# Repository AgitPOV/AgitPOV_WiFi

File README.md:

#  AgitPOV Wifi: 24-RGB LED dual sided POV with Wifi (ESP8266)

 (c) 2011-2017
 Contributors over the years for this version

* Thomas Ouellet Fredericks - Debuging, Accelerometer and LED engine and animation code
* Alexandre Castonguay
* Andre Girard andre@andre-girard.com
* Alan Kwok
* Sofian Audry
* Mariangela Aponte Nuñez
* Jean-Pascal Bellemare
* Daniel Felipe Valencia dfvalen0223@gmail.com
* Alex Keeling

[FR] Cette version utilise une puce ESP8266 qui permet de programmer un mot à partir de n'importe quelle connexion WiFi.
Les DELs RVB seront pré-assemblées pour que les ateliers se concentrent sur la sélection des mots que nous aimerions voir
dans nos roues de vélo, et de passer plus de temps à parcourir la ville. Les batteries sont rechargeables donc les POVs 
seront utiles plus longtemps et finalement, nous travaillons avec un designer industriel qui va développer un boitier résistant, 
imperméable et facile à placer et retirer des rayons. Tous les fichiers sont ici et nous produisons les plaquettes et les 
boitiers sous peu!

[ES] Este versión usa a un ESP8266 que permite de programar una palabra desde un dispositivo WiFi. Usamos DELs 
premontados porque los talleres se vuelven en intercambios sobre las palabras que quérémos ver en nuestra ruedas 
de bicicletas y también de pasar más tiempo juntas en una rodada. Baterías están rescargable y trabajamos con un 
diseñador sobre cajas, durables, resistente al agua y fácil de poner y quitar de los rayos de nuestras bicis. Los 
archivos están aquí y vamos a producir los plaquetas y cajas de pronto!

[EN] This version uses an ESP8266 board that let's you program your word from a WiFi device. Surface mount RGB LEDs 
(APA102C) are already soldered so we spend more time discussing what words to put on our bikes and get more time out 
in the city together. The batteries are rechargeable so people can keep using their POVs longer. Finally, we are working 
with an industrial designer so we can get sturdy, water resistant cases that are easy to put in and out of your spokes. 
All the basic files are here and we'll let you know when the boards and cases are ready!

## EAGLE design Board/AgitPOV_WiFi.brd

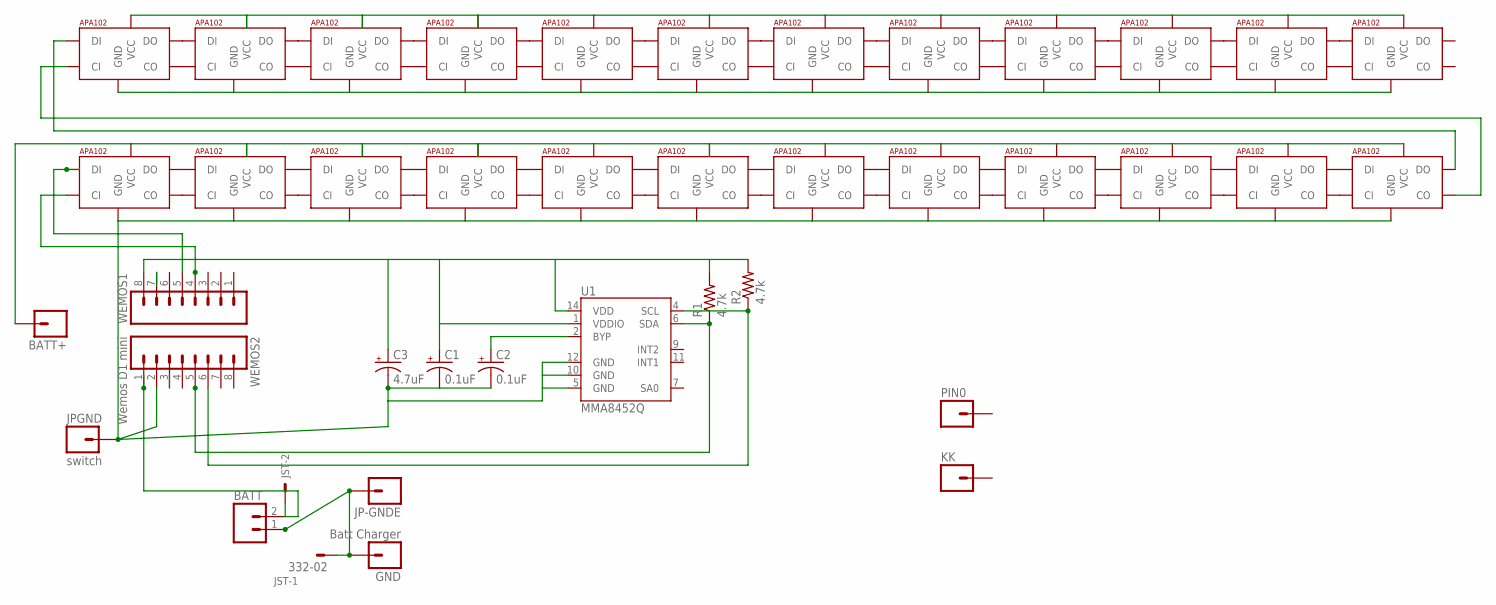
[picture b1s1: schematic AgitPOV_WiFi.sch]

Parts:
BATT: M02LOCK_LONGPADS; 1X02_LOCK_LONGPADS
BATT+: M01PTH; 1X01
C1, C2: 0.1uF; EIA3216
C3: 4.7uF; EIA3216
DEL1, DEL2, DEL3, DEL4, DEL5, DEL6, DEL7, DEL8, DEL9, DEL10, DEL11, DEL12, DEL13, DEL15, DEL16, DEL17, DEL18, DEL19, DEL20, DEL21, DEL22, DEL23, DEL24: APA1025050; APA102_5050
FFFFF: APA1025050; APA102_5050
GND: Batt Charger; 1X01
JP-GNDE: M01PTH; 1X01
JPGND: switch; 1X01
JST: 332-02
KK: M01PTH; 1X01
PIN0: M01PTH; 1X01
R1, R2: 4.7k; 1206
U1: MMA8452Q; QFN-16_0.5MM
WEMOS1: M08; 1X08_ROUND
WEMOS2: Wemos D1 mini; 1X08_ROUND

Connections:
5V: BATT.2, BATT+.1, DEL1.1 (VCC), DEL2.1 (VCC), DEL3.1 (VCC), DEL4.1 (VCC), DEL5.1 (VCC), DEL6.1 (VCC), DEL7.1 (VCC), DEL8.1 (VCC), DEL9.1 (VCC), DEL10.1 (VCC), DEL11.1 (VCC), DEL12.1 (VCC), DEL13.1 (VCC), DEL15.1 (VCC), DEL16.1 (VCC), DEL17.1 (VCC), DEL18.1 (VCC), DEL19.1 (VCC), DEL20.1 (VCC), DEL21.1 (VCC), DEL22.1 (VCC), DEL23.1 (VCC), DEL24.1 (VCC), FFFFF.1 (VCC), JST.2, WEMOS2.1
+3.3V: C1.A (+), C3.A (+), R1.2, R2.2, U1.1 (VDDIO), U1.14 (VDD), WEMOS1.8
BYP: C2.A (+), U1.2 (BYP)
ENTREEGND: BATT.1, GND.1, JP-GNDE.1, JST.1
GND: C1.C (-), C2.C (-), C3.C (-), DEL1.6 (GND), DEL2.6 (GND), DEL3.6 (GND), DEL4.6 (GND), DEL5.6 (GND), DEL6.6 (GND), DEL7.6 (GND), DEL8.6 (GND), DEL9.6 (GND), DEL10.6 (GND), DEL11.6 (GND), DEL12.6 (GND), DEL13.6 (GND), DEL15.6 (GND), DEL16.6 (GND), DEL17.6 (GND), DEL18.6 (GND), DEL19.6 (GND), DEL20.6 (GND), DEL21.6 (GND), DEL22.6 (GND), DEL23.6 (GND), DEL24.6 (GND), FFFFF.6 (GND), JPGND.1, U1.5 (GND), U1.10 (GND), U1.12 (GND), WEMOS2.2
unnamed: DEL1.5 (CI), WEMOS1.4
unnamed: DEL1.4 (DI), WEMOS1.5
unnamed: DEL12.2 (CO), DEL13.5 (CI)
unnamed: DEL2.2 (CO), DEL3.5 (CI)
unnamed: DEL2.3 (DO), DEL3.4 (DI)
unnamed: DEL1.3 (DO), DEL2.4 (DI)
unnamed: DEL1.2 (CO), DEL2.5 (CI)
unnamed: DEL3.3 (DO), DEL4.4 (DI)
unnamed: DEL3.2 (CO), DEL4.5 (CI)
unnamed: DEL4.3 (DO), DEL5.4 (DI)
unnamed: DEL4.2 (CO), DEL5.5 (CI)
unnamed: DEL5.3 (DO), DEL6.4 (DI)
unnamed: DEL5.2 (CO), DEL6.5 (CI)
unnamed: DEL6.3 (DO), DEL7.4 (DI)
unnamed: DEL6.2 (CO), DEL7.5 (CI)
unnamed: DEL7.3 (DO), DEL8.4 (DI)
unnamed: DEL7.2 (CO), DEL8.5 (CI)
unnamed: DEL8.3 (DO), DEL9.4 (DI)
unnamed: DEL8.2 (CO), DEL9.5 (CI)
unnamed: DEL9.3 (DO), DEL10.4 (DI)
unnamed: DEL9.2 (CO), DEL10.5 (CI)
unnamed: DEL10.3 (DO), DEL11.4 (DI)
unnamed: DEL10.2 (CO), DEL11.5 (CI)
unnamed: DEL11.3 (DO), DEL12.4 (DI)
unnamed: DEL11.2 (CO), DEL12.5 (CI)
unnamed: DEL12.3 (DO), DEL13.4 (DI)
unnamed: DEL15.5 (CI), FFFFF.2 (CO)
unnamed: DEL15.4 (DI), FFFFF.3 (DO)
unnamed: DEL13.3 (DO), FFFFF.4 (DI)
unnamed: DEL13.2 (CO), FFFFF.5 (CI)
unnamed: DEL15.3 (DO), DEL16.4 (DI)
unnamed: DEL15.2 (CO), DEL16.5 (CI)
unnamed: DEL16.3 (DO), DEL17.4 (DI)
unnamed: DEL16.2 (CO), DEL17.5 (CI)
unnamed: DEL17.3 (DO), DEL18.4 (DI)
unnamed: DEL17.2 (CO), DEL18.5 (CI)
unnamed: DEL18.3 (DO), DEL19.4 (DI)
unnamed: DEL18.2 (CO), DEL19.5 (CI)
unnamed: DEL19.3 (DO), DEL20.4 (DI)
unnamed: DEL19.2 (CO), DEL20.5 (CI)
unnamed: DEL20.3 (DO), DEL21.4 (DI)
unnamed: DEL20.2 (CO), DEL21.5 (CI)
unnamed: DEL21.3 (DO), DEL22.4 (DI)
unnamed: DEL21.2 (CO), DEL22.5 (CI)
unnamed: DEL22.3 (DO), DEL23.4 (DI)
unnamed: DEL22.2 (CO), DEL23.5 (CI)
unnamed: DEL23.3 (DO), DEL24.4 (DI)
unnamed: DEL23.2 (CO), DEL24.5 (CI)
SCL: R2.1, U1.4 (SCL), WEMOS2.6
SDA: R1.1, U1.6 (SDA), WEMOS2.5

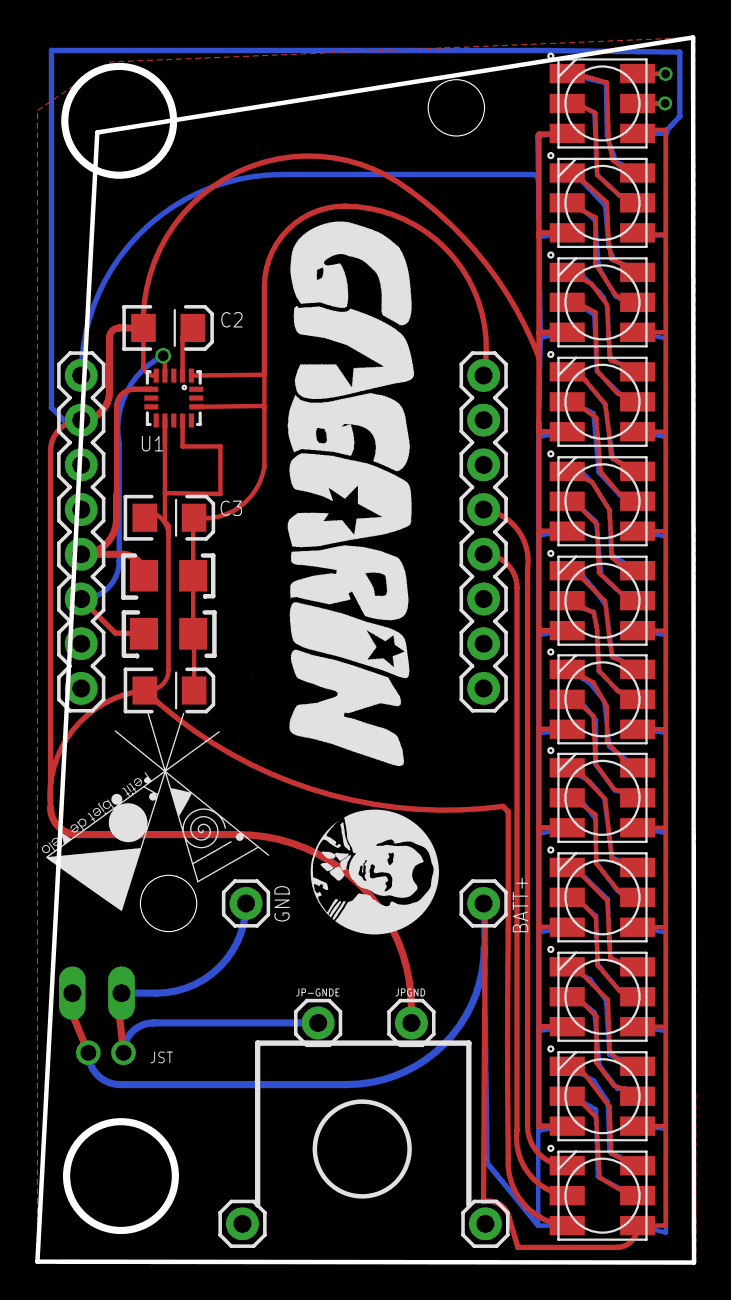
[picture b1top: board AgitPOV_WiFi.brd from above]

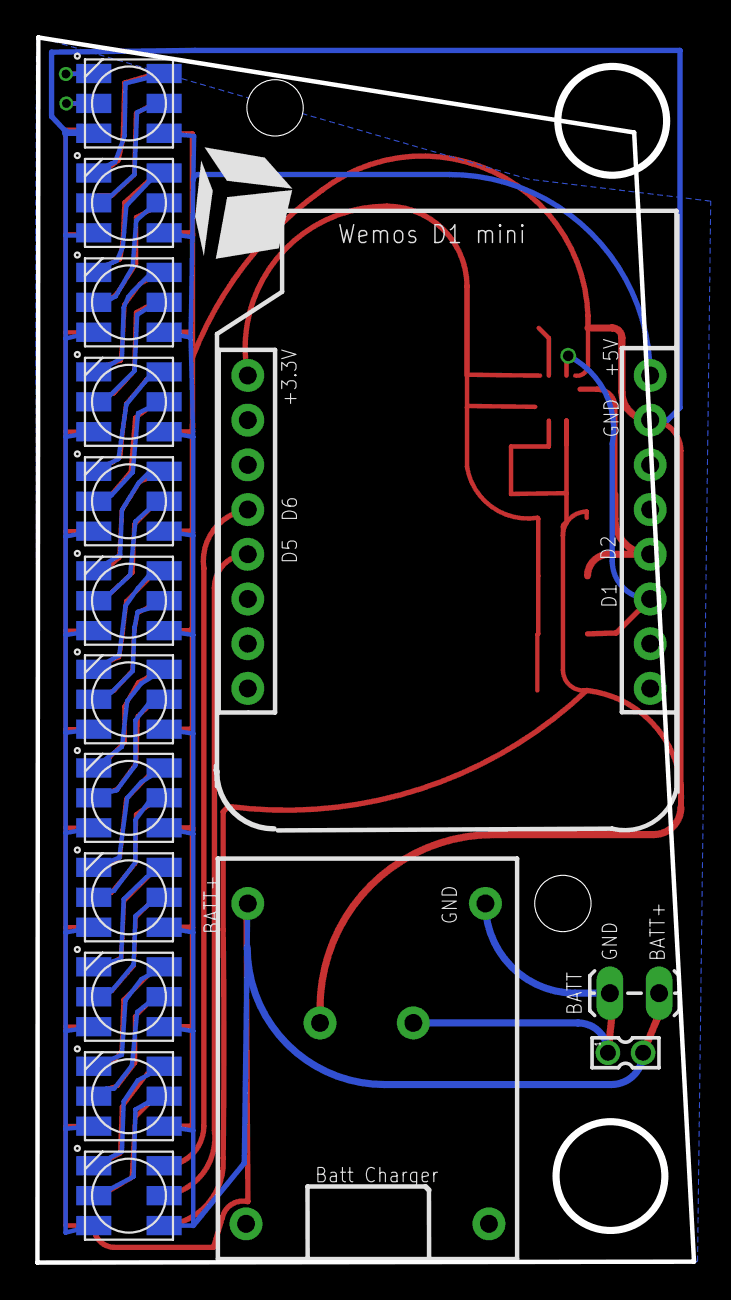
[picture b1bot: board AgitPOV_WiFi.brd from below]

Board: 2 copper layers, 37.1 x 69.4 mm, 40 parts (14 on the bottom side), 55 nets.

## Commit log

2017-01-10 Eagle files
2017-01-10 Arduino file
    * ESP8266Wifi
    * WifiClient
    * Uses D3 for the interrupt
    * APA102C RGB LEDs
2017-01-10 First Bill of Materials
2017-01-10 images
2017-01-16 Attempting to add a complete font w. special chars
    Ajouté la licence et les contributeurs au projet
    Merci à Alex Keeling, il reste des erreurs dans la détection de byte dans nouveauArray() mais c'est un bon début.
2017-01-16 Au bon endroit...
    Added Contributors
    Added the licence
    Attempt at a complete font, errors in nouveauArray()
2017-01-23 avec acceleromètre
2017-01-23 With an option (untested) of an accelerometer.
2017-01-25 Tout à sa place
2017-01-26 added a capacitor for the accelerometer, DRChecked
2017-01-26 proper ACCEL integration
2017-02-14 organisation
    - removed calls to extraneous libraries
    - server functions are in AgitServer
2017-02-16 Ya con 'extended' UTF-8 chars...ufff
2017-02-20 selection, indication, organisation
    AgitDot : new patterns with more time for serving the page
    AgitFichier : prep for multiple files writing and selection
2017-02-20 Changed the interrupt pin from D3 to D7
    D3 (and D4) when pulled to GND will prevent the Wemos from booting :/.
2017-02-20 Post-coffee commit
2017-02-21 Sin interrupt para el ACCEL! De regresar al sensor Hall en D4.
2017-02-21 More integration, Hall sensor enabled on pin D4
2017-02-21 Swapped the MMA7660 for the MMA8452Q
2017-02-21 Added pin headers for INT1 and INT2
2017-02-23 Updated with the MMA8452 accelerometer
2017-03-14 Revert "Added gitignore"
    This reverts commit 2947c8999836a2c1890e0c695ff4fb373fb22d62.
2017-03-14 Added gitignore
2017-03-14 Added UDP test and Accelerometer code
2017-03-14 Added documentation
2017-03-19 essais avec l'accéléromètre
    UDP_Accelerometer.ino :
    Promising use of atan2 to get the angle from the accel.cx and
    access.cy values
    Values in X max out quickly (tilt over +8G)
    Y values are used instead
    Added a smoothing routine
2017-03-20 nouvelle version
2017-03-20 Added lowpass and speed analysis
2017-03-20 Tydied up the code
2017-03-20 More lowpassness
2017-03-20 Fixed error with previous variables
2017-03-20 Added an example with FastLed
2017-03-20 Tests
2017-03-20 tests avec PD
    la version _2 est instable pour le wifi?
2017-03-20 test
2017-03-20 fuck
2017-03-20 Reverting
2017-03-20 Fixing bad merge
2017-03-20 Making my changes are there
2017-03-21 Mean and lean board
2017-03-25 Ajustement pour le tableau des caractères spéciaux
    Nouveau board
2017-03-26 Retire tout ce qui a à voir avec le bouton et le capteur Hall
2017-03-26 Préparation pour inverser l'ordre des rangées de DELs
2017-03-26 Adaptation
2017-03-28 New board version, FastLED display works.
    Board : removed button, Hall sensor, back to smd switch, cleaning
    around the accelerometer, removed int1 + int2, one less via! More space
    for the LEDs -> resized board.
    FastLED : correct GRB color space, bizarro world to display text on
    both sides.
2017-04-04 Début de l'application
    Cordova avalanche
2017-04-04 Modélisation et code pour l'cccl
2017-04-04 logo
2017-04-04 carcinero
2017-04-16 Ios et android AgitPOV app
2017-04-16 Changements à la plaquette
2017-04-16 icons for the app
2017-04-16 un poco de color
2017-04-16 splash screen icon
2017-04-16 meilleur cadrage
2017-04-16 resize splash
2017-04-16 submit word from the app
2017-04-16 reboot ios
2017-04-16 icônes de nouveau
2017-04-16 cordova
2017-04-16 cordova 06
2017-04-16 cordova 07
2017-04-16 cordova 08
2017-04-16 cordova 09
2017-04-17 cordova 10
2017-04-17 cordova 11
2017-04-17 cordova 12
2017-04-17 cordova 13
2017-04-17 cordova 14
2017-04-17 cordova 15
2017-04-17 cordova 16
2017-04-23 iOS app
2017-06-23 Cambios desde Manizales y Cartagena
    - luz de colores en la pagina html
    - individual AP desde el MAC address
2017-06-24 Medellin Panama Newark
    intégration du code de Thomas
2017-07-07 intégration du code de Thomas
2017-07-08 Havre-aux-maisons 02
    - couleur persistante
    - persistent palabra
    - povIntervalColumns pour l’ajustement de la vitesse d’affichage
2017-07-11 hamac app
    - sauvegarde des icônes
    - préparation pour les apps
2017-07-11 2e hamac page
2017-07-19 arcoiris update (-) apps
    - retirer le code des apps
    - ajout du code de arcoris
    - formattage de la page html servie par le POV
2017-07-21 auto placement files
2017-08-08 Rainbow
2017-08-08 Getting ready to change the way characters are converted to matrix data
2017-08-08 Fixed bugs and shit
2017-08-09 Added a nice color selection animation
2017-08-09 Added shake detection to cancel Wifi AP
2017-08-11 Fixed bug about rotation of wheel and changed AP name
2017-08-11 Clean up
2017-08-14 Everything seems to work okay...
2017-08-14 Trying to make it work on OS X
2017-08-15 Removed UDP debug
2017-08-15 Removed x from wheel
2017-08-15 A little cleanup
2017-08-15 un peu plus de style informatif
2017-08-15 Parts costs for 1000 units
2017-08-15 Added a date tage
2017-08-15 couleurs
2017-08-15 Ajout de la vitesse dans FrameAccelerator et modification de la détection de trigger
2017-08-15 essai de sync sans ajouter mes changements à
    AgitPOVWIFI.ino
    FrameAccelerator.h
2017-08-15 essai pour restreindre les caractères
2017-08-18 Changed some settings to make it work better
2017-08-18 Modified gitignore
2017-09-03 grande roue
    ajout du code pour la grande roue
2017-09-03 cleaning my mess
2017-09-04 dernière minute
    (presque)
2017-09-05 filtres et écarts types
2017-09-09 mathieu #3
    Les accents et bug frameCount
2017-10-06 fin pour le rouge
2019-07-22 Analysis and improvements to the lop
    Implementation of spiffs accelerometer data saving (careful, there is a
    200ms hit for every writing)
    Scripts for gnuplot to analyze the data
    Improvements to the low pass filter
2019-10-20 Dark design mode
    Meilleure constance de l’affichage
    Le ‘mode sombre’ ajouté, parfait pour les espaces sombres intérieurs
2022-07-09 Ukraina mode
    Un guia para otras colores

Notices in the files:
parts and their libraries:
SparkFun-Connectors: Licensing: Creative Commons ShareAlike 4.0 International - https://creativecommons.org/licenses/by-sa/4.0
